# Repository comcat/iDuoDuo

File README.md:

iDuoDuo - Pet APRS Tracker
=======================================

More photo of My DuoDuo :) [My DuoDuo Life](http://comcat.lofter.com/tag/%E5%A4%9A%E5%A4%9A)

[*iDuoDuo Board*](http://jackslab.org/)

Features
-------------------
* ATMEGA328p MCU, Arduino compatible
* 1W VHF radio module, low cost, about $5 ([SR_FRS_1WV](https://item.taobao.com/item.htm?id=21278567784))
* 1200 bauds AFSK using 8-bit PWM
* Sends out standard APRS position messages
* mini GPS module
* 18650 power supply
* Open Source hardware and firmware 

Pin map
-------------------
iDuoDuo board

* D3 is the audio out pin
* D4 is the PTT pin
* D12 is the PD pin of radio module
* D13 is the PWR_CTRL pin of the radio module

* D8 is the power on input pin
* D9 is the power on output pin

Repository Contents
-------------------
* hardware/ - All Eagle design files (.brd, .sch) and Gerber files of iDuoDuo Board 
* firmware/ - Firmware source files of the iDuoDuo

Product Versions
----------------
* [IDuoDuo-V0.4](hardware/V0.4/) - Stupid bug of the S1 key package. 2016/02/09
* [IDuoDuo-V0.6](hardware/V0.6/) - work OK.

License Information
-------------------
The hardware is released under [Creative Commons ShareAlike 4.0 International](https://creativecommons.org/licenses/by-sa/4.0/).

Distributed as-is; no warranty is given.

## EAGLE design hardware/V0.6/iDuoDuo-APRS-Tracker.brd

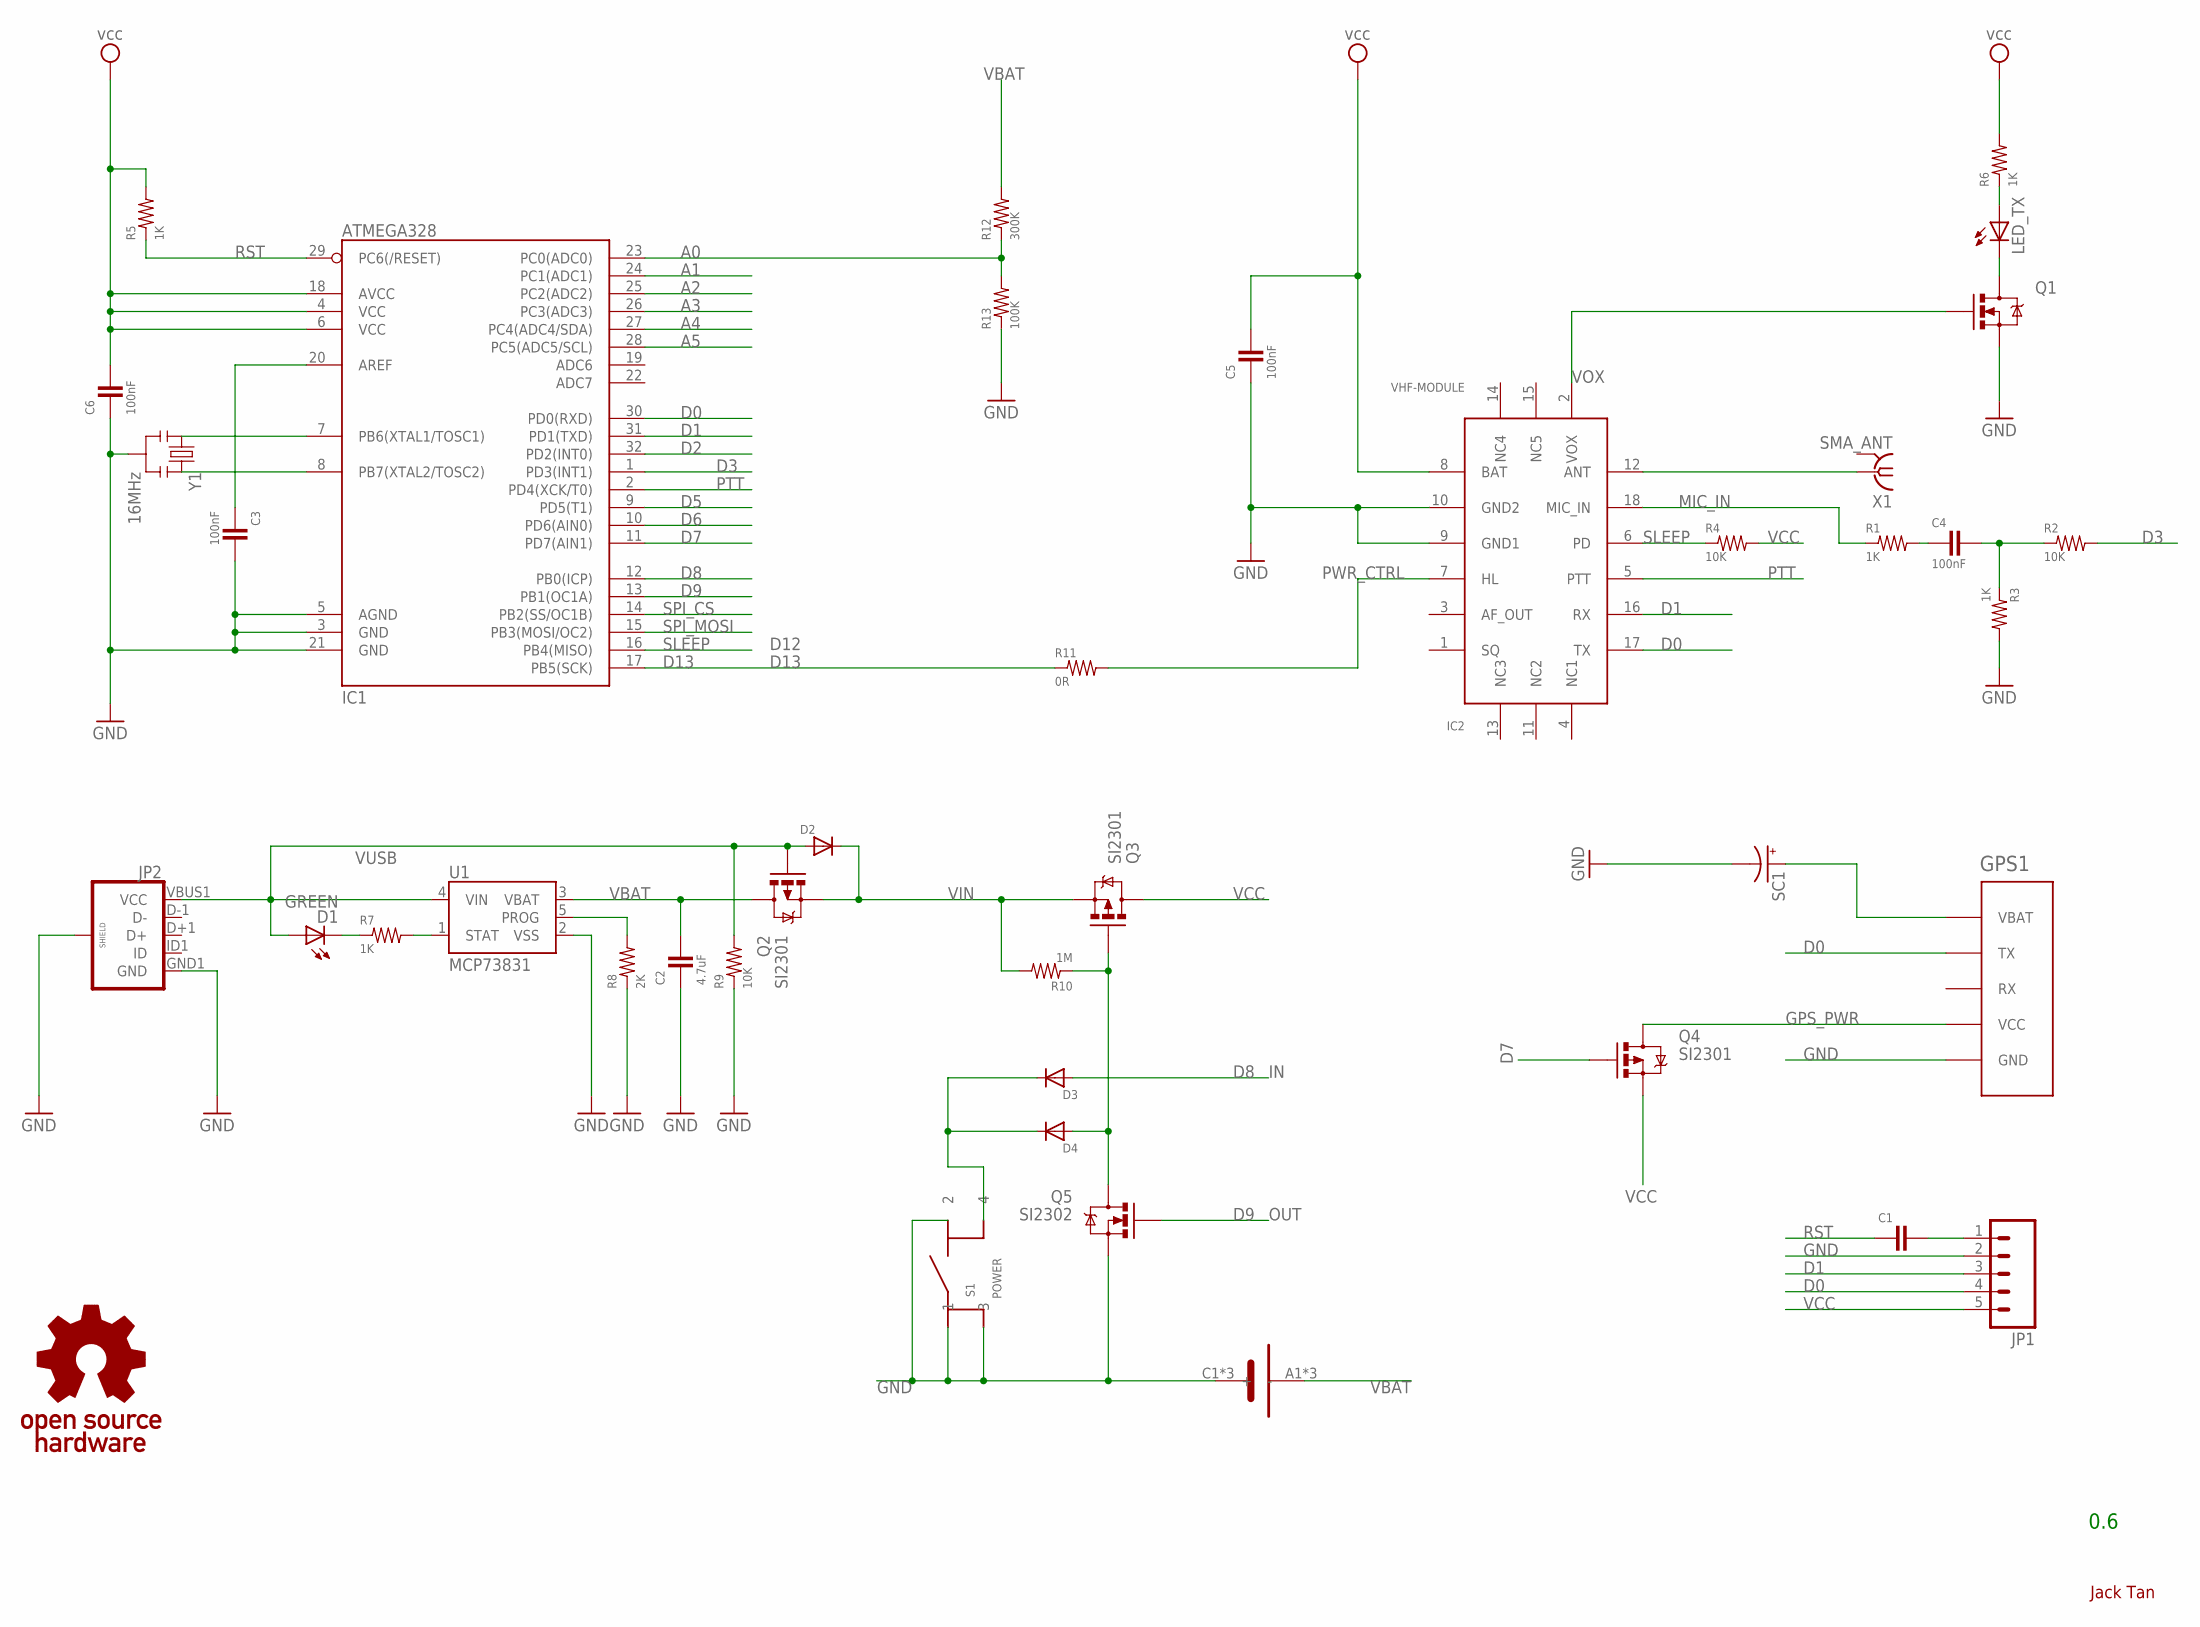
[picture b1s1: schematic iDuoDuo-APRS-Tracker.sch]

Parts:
B1: 18650
C1: 0603-CAP
C2: 4.7uF; 0603-CAP
C3, C4, C5, C6: 100nF; 0603-CAP
D1: GREEN; LED3MM
D2, D3, D4: DIODESOD; SOD-323
GPS1: GAM-1433
IC1: ATMEGA328; TQFP32-08
IC2: VHF-MODULE
JP1: M05PTH; 1X05
JP2: USB_MICROB_PLUGCONN-11752; USB-B-MICRO-SMD_V03
LED_TX: LED3MM
Q1: MOSFET-N-SMD; SOT23-3
Q2, Q3, Q4: SI2301; SOT23
Q5: SI2302; SOT23-3
R1, R3, R5, R6, R7: 1K; 0603-RES
R2, R4, R9: 10K; 0603-RES
R8: 2K; 0603-RES
R10: 1M; 0603-RES
R11: 0R; 0603-RES
R12: 300K; 0402-RES
R13: 100K; 0402-RES
S1: POWER; SWITCH-TS-038
SC1: SC-3.3-0.22F
U1: MCP73831; SOT23-5
U$1: OPEN_HARDWARE_LOGO
X1: SMA_ANT; SMA-KE
Y1: 16MHz; RESONATOR-SMD

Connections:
A0: IC1.23 (PC0(ADC0)), R12.1, R13.2
A1: IC1.24 (PC1(ADC1))
A2: IC1.25 (PC2(ADC2))
A3: IC1.26 (PC3(ADC3))
A4: IC1.27 (PC4(ADC4/SDA))
A5: IC1.28 (PC5(ADC5/SCL))
D0: GPS1.P$2 (TX), IC1.30 (PD0(RXD)), IC2.17 (TX), JP1.4
D1: IC1.31 (PD1(TXD)), IC2.16 (RX), JP1.3
D2: IC1.32 (PD2(INT0))
D3: IC1.1 (PD3(INT1)), R2.2
D5: IC1.9 (PD5(T1))
D6: IC1.10 (PD6(AIN0))
D7: IC1.11 (PD7(AIN1)), Q4.1 (G)
D8: D3.2 (A), IC1.12 (PB0(ICP))
D9: IC1.13 (PB1(OC1A)), Q5.1 (G)
D13: IC1.17 (PB5(SCK)), R11.1
GND: B1.C1 (-), B1.C2 (-), B1.C3 (-), C2.1, C3.2, C5.1, C6.1, GPS1.P$5 (GND), IC1.3 (GND), IC1.5 (AGND), IC1.21 (GND), IC2.9 (GND1), IC2.10 (GND2), JP1.2, JP2.GND1 (GND), JP2.SHIELD1 (SHIELD), JP2.SHIELD2 (SHIELD), JP2.SHIELD3 (SHIELD), Q1.2 (S), Q5.2 (S), R3.2, R8.1, R9.1, R13.1, S1.1, S1.2, S1.3, SC1.2 (-), U1.2 (VSS), X1.G@1 (GND), X1.G@2 (GND), X1.G@3 (GND), X1.G@4 (GND), Y1.2
GPS_PWR: GPS1.P$4 (VCC), Q4.3 (D)
MIC_IN: IC2.18 (MIC_IN), R1.1
unnamed: IC1.7 (PB6(XTAL1/TOSC1)), Y1.1
unnamed: IC1.8 (PB7(XTAL2/TOSC2)), Y1.3
unnamed: IC2.12 (ANT), X1.1
unnamed: C4.1, R1.2
unnamed: C4.2, R2.1, R3.1
unnamed: C3.1, IC1.20 (AREF)
unnamed: D4.2 (A), Q3.1 (G), Q5.3 (D), R10.1
unnamed: LED_TX.K (C), Q1.3 (D)
unnamed: LED_TX.A, R6.1
unnamed: GPS1.P$1 (VBAT), SC1.1 (+)
unnamed: C1.2, JP1.1
unnamed: D1.K (C), R7.1
unnamed: R7.2, U1.1 (STAT)
unnamed: R8.2, U1.5 (PROG)
unnamed: D3.1 (C), D4.1 (C), S1.4
PTT: IC1.2 (PD4(XCK/T0)), IC2.5 (PTT)
PWR_CTRL: IC2.7 (HL), R11.2
RST: C1.1, IC1.29 (PC6(/RESET)), R5.1
SLEEP: IC1.16 (PB4(MISO)), IC2.6 (PD), R4.1
SPI_CS: IC1.14 (PB2(SS/OC1B))
SPI_MOSI: IC1.15 (PB3(MOSI/OC2))
VBAT: B1.A1 (+), B1.A2 (+), B1.A3 (+), C2.2, Q2.3 (D), R12.2, U1.3 (VBAT)
VCC: C5.2, C6.2, IC1.4 (VCC), IC1.6 (VCC), IC1.18 (AVCC), IC2.8 (BAT), JP1.5, Q3.3 (D), Q4.2 (S), R4.2, R5.2, R6.2
VIN: D2.1 (C), Q2.2 (S), Q3.2 (S), R10.2
VOX: IC2.2 (VOX), Q1.1 (G)
VUSB: D1.A, D2.2 (A), JP2.VBUS1 (VCC), Q2.1 (G), R9.2, U1.4 (VIN)

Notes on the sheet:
0.6
Jack Tan
OUT
D12
D13

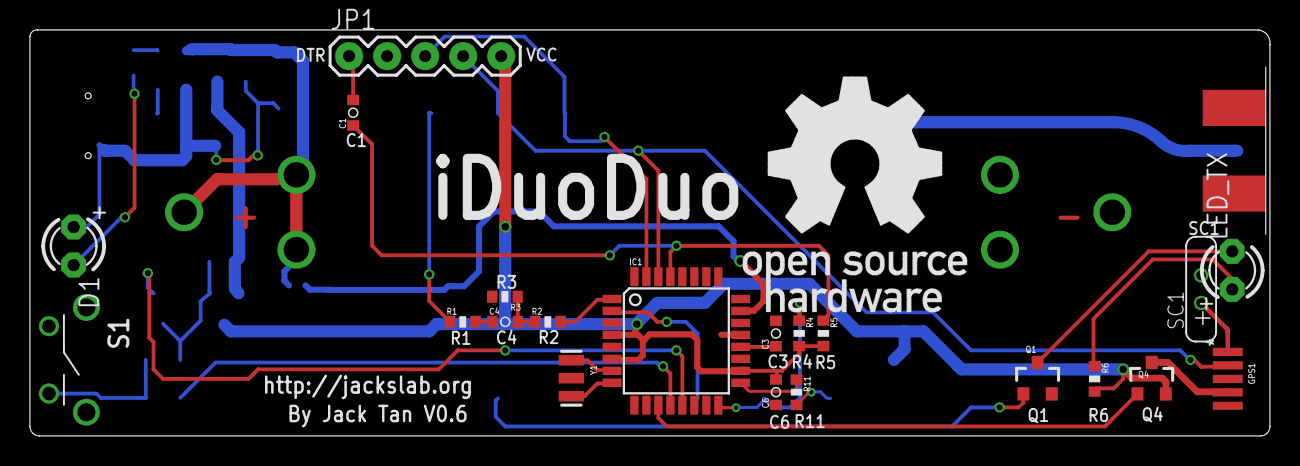
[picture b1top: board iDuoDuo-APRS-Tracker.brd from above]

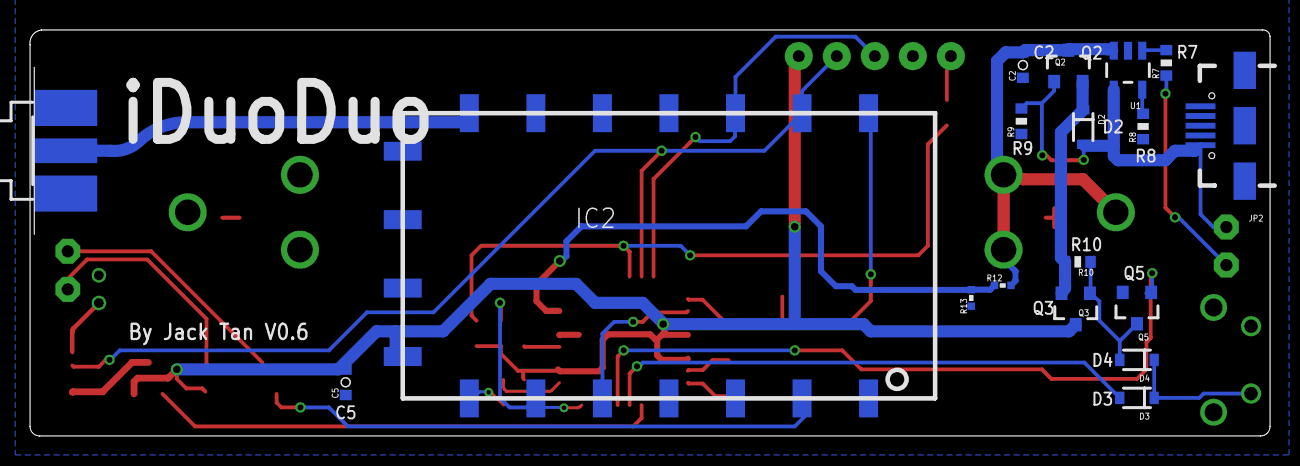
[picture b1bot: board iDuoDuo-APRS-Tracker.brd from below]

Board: 2 copper layers, 82.8 x 27.1 mm, 41 parts (18 on the bottom side), 35 nets.

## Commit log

2016-02-09 hardware: add Eagle design files (*.sch and *.brd) of v0.4
2016-02-09 hardware: add the gerber files of v0.4
2016-02-09 hardware: export image of the eagle design
2016-02-09 doc: add a readme
2016-02-09 doc: update the readme
2018-10-17 first firmware commit based on trackuino v1.4
2018-10-17 Modify for testing the VHF module
    disable the GPS code.
2018-10-17 change the callsign and aprs symbol
    using the 'DUODUO-9' as the testing callsign
    using the 'Rover' (a dog icon in map) symbol
2018-10-17 remove the useless radio file hx1
    hx1 is expensive
2018-10-17 add a radio module named DMO
    It's a VHF/UHF 1W radio module. The price is about $10
2018-10-17 remove the useless pic32 files
2018-10-17 Try to add the method function set_freq of Radio module
    Now we use the PIN 1 (UART TX) as the transmit pin to send
    the AT CMDs to the Radio Module.
2018-10-17 set the aprs comment to EPRS
    we use the '>EPRS=' to connect to the EPRS
2018-10-17 disable the led pin
2018-10-17 suppot iGoGo board
    * D3 is the audio out pin
    * D4 is the PTT pin
    * D12 is the PD pin of radio module
    * D13 is the PWR_CTRL pin of the radio module
    * D8 is the power on input pin
    * D9 is the power on output pin
2018-10-17 try to add the power on support
2018-10-17 fixup the build error
2018-10-17 firmware: rename the trackuino to firmware.pde
2018-10-17 enable debuging gps
2018-10-17 firmware: update the readme
2019-06-01 hardware: remove the gerber files of v0.4
    There a stupid error about the package of the key...
2019-06-01 rename the iGoGo to iDuoDuo
2019-06-01 hardware: remove the gerber files directory
2019-06-01 doc: update the image files
2019-06-01 hardware: add a new version v0.6
    fixed the stupid bug of S1 key package
2019-06-01 hardware: fix the gps switch bug of v0.6
2019-06-01 doc: update readme
2019-06-01 firmware: add a macro switch to disable the gps for testing
2019-06-01 firmware: add the cores and libs of arduino-0022
    add a makefile to support compiling from cmdline
2019-06-01 firmware: try to fix the build error when use the new toolchain
2019-06-01 firmware: support the old toolchain (arduino-0022)
2019-06-01 firmware: update the Makefile.22
2019-06-01 firmware: using the arduino-0022 build system by default
